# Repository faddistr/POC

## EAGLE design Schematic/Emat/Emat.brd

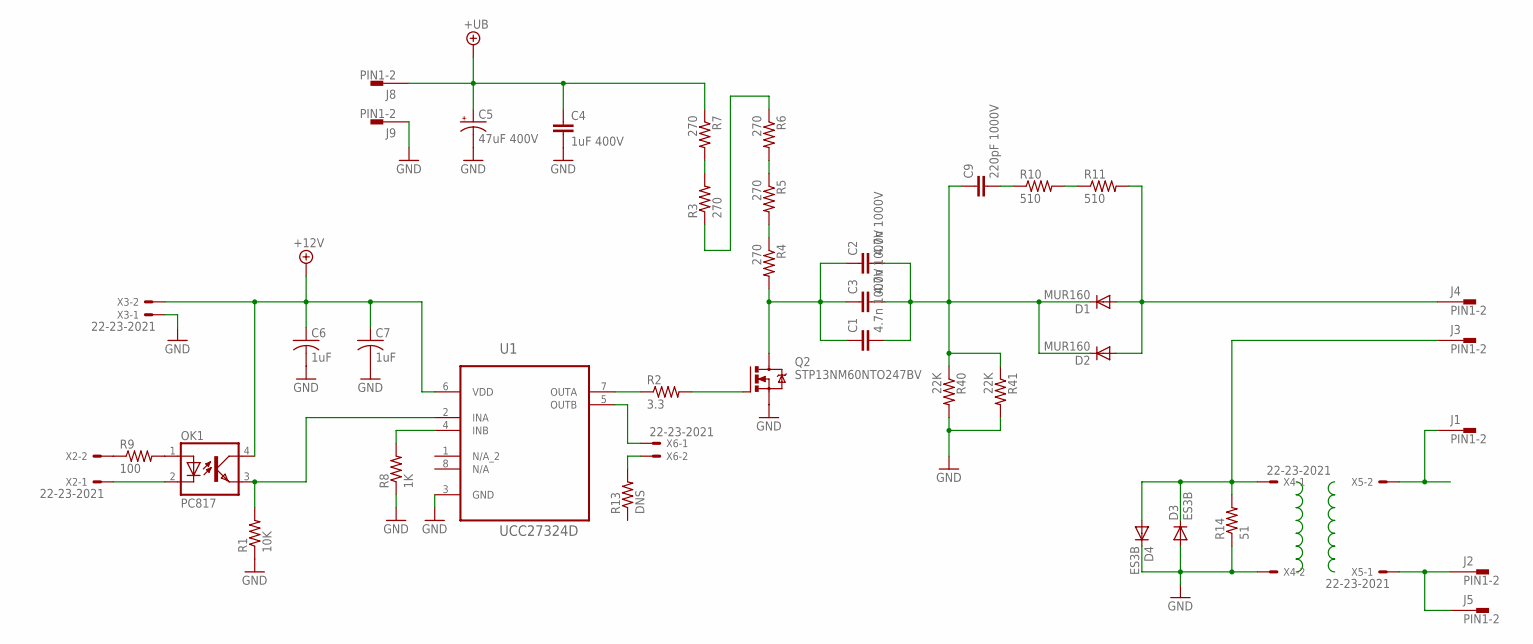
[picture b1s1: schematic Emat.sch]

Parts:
C1, C2, C3: 4.7n 1000V; C10B4
C4: 1uF 400V; C27.5B13
C5: 47uF 400V; SANYO-OSCON_G
C6, C7: 1uF; C0805
C9: 220pF 1000V; C075-042X103
D1, D2: MUR160; DO41-10
D3, D4: ES3B; SMC
J1, J2, J3, J4, J5, J8, J9: PIN1-2; 62221
OK1: PC817; DIL04
Q2: STP13NM60NTO247BV; TO247BV
R1: 10K; R1206
R2: 3.3; R1206
R3, R4, R5, R6, R7: 270; R2512
R8: 1K; R1206
R9: 100; R1206
R10, R11: 510; R1206
R13: DNS; R1206
R14: 51; R1206
R40, R41: 22K; R2512
U1: UCC27324D; SOIC127P600X175-8N
X2, X3, X4, X5, X6: 22-23-2021

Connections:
+12V: C6.1, C7.1, OK1.4 (COL), U1.6 (VDD), X3.2
+UB: C4.1, C5.+, J8.1, R7.1
GND: C4.2, C5.-, C6.2, C7.2, D3.A, D4.C, J9.1, Q2.S, R1.1, R8.1, R14.1, R40.2, R41.2, U1.3 (GND), X3.1, X4.2
unnamed: OK1.3 (EMIT), R1.2, U1.2 (INA)
unnamed: R2.1, U1.7 (OUTA)
unnamed: Q2.G, R2.2
unnamed: C1.1, C2.1, C3.1, Q2.D, R4.2
unnamed: R4.1, R5.2
unnamed: R5.1, R6.2
unnamed: R3.1, R6.1
unnamed: R3.2, R7.2
unnamed: J1.1, X5.2
unnamed: R8.2, U1.4 (INB)
unnamed: U1.5 (OUTB), X6.1
unnamed: C9.2, R10.1
unnamed: R10.2, R11.1
unnamed: D1.A, D2.A, J4.1, R11.2
unnamed: C1.2, C2.2, C3.2, C9.1, D1.C, D2.C, R40.1, R41.1
unnamed: OK1.1 (A), R9.2
unnamed: R9.1, X2.2
unnamed: OK1.2 (C), X2.1
unnamed: D3.C, D4.A, J3.1, R14.2, X4.1
unnamed: R13.2, X6.2
unnamed: J2.1, J5.1, X5.1

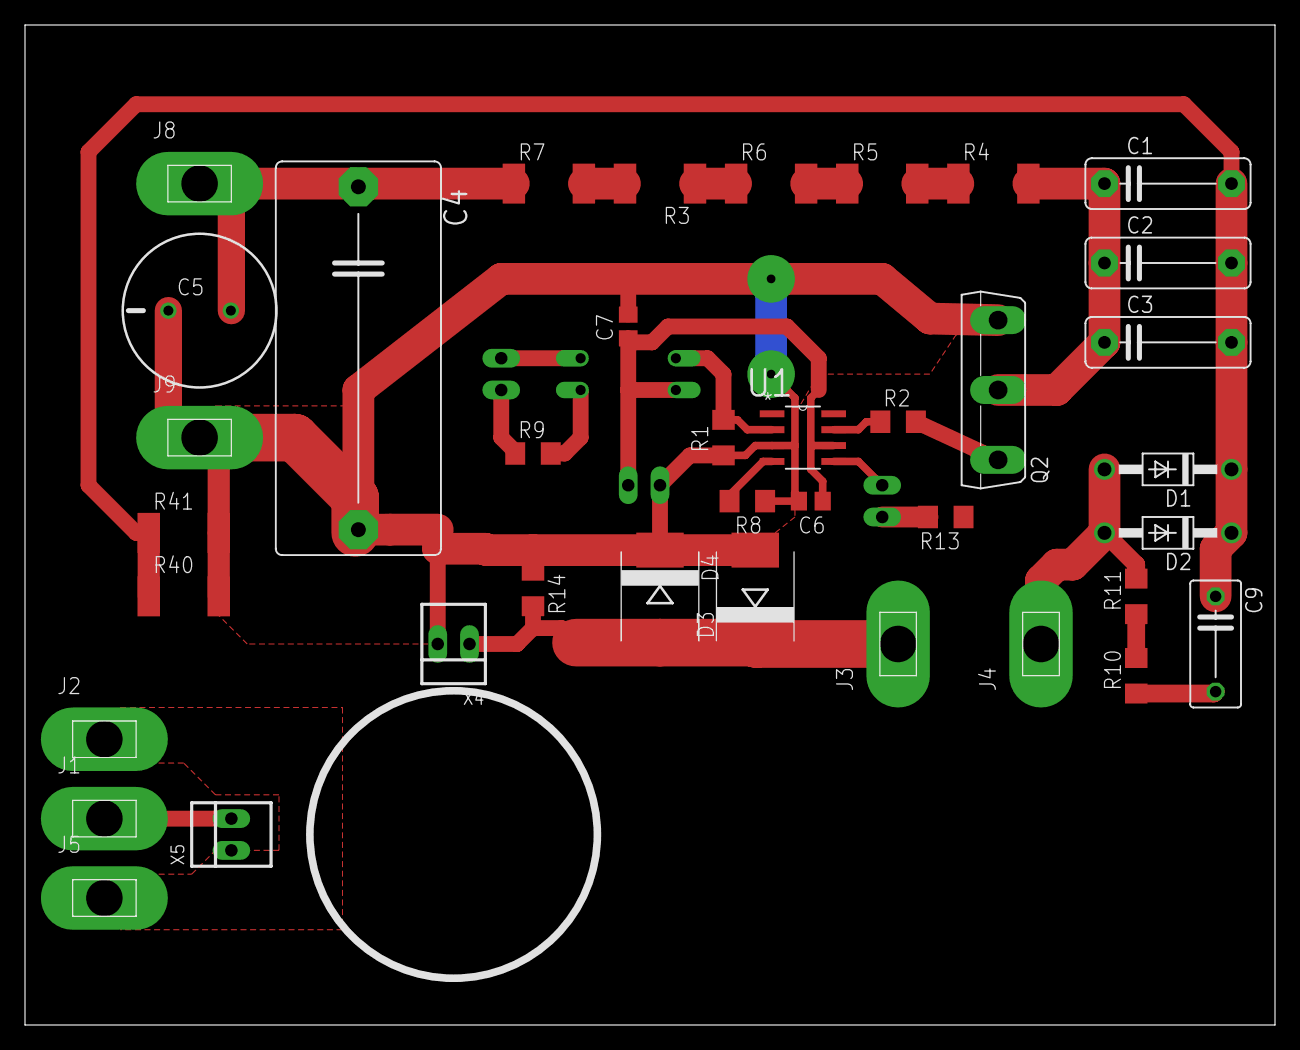
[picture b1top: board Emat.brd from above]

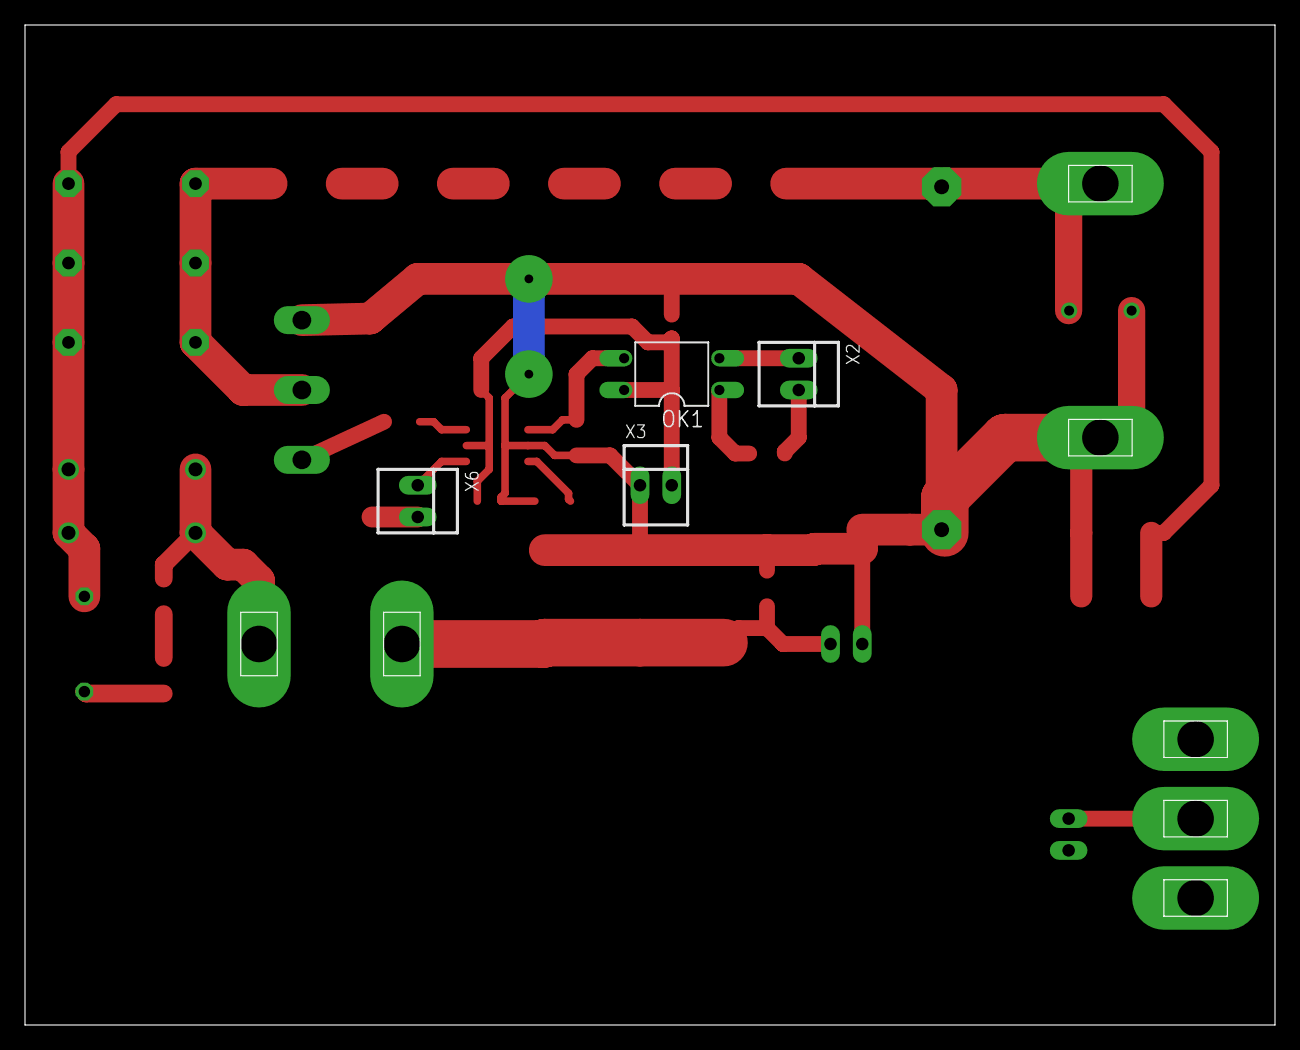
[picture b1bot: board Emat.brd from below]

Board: 2 copper layers, 100.0 x 80.0 mm, 42 parts (4 on the bottom side), 24 nets.

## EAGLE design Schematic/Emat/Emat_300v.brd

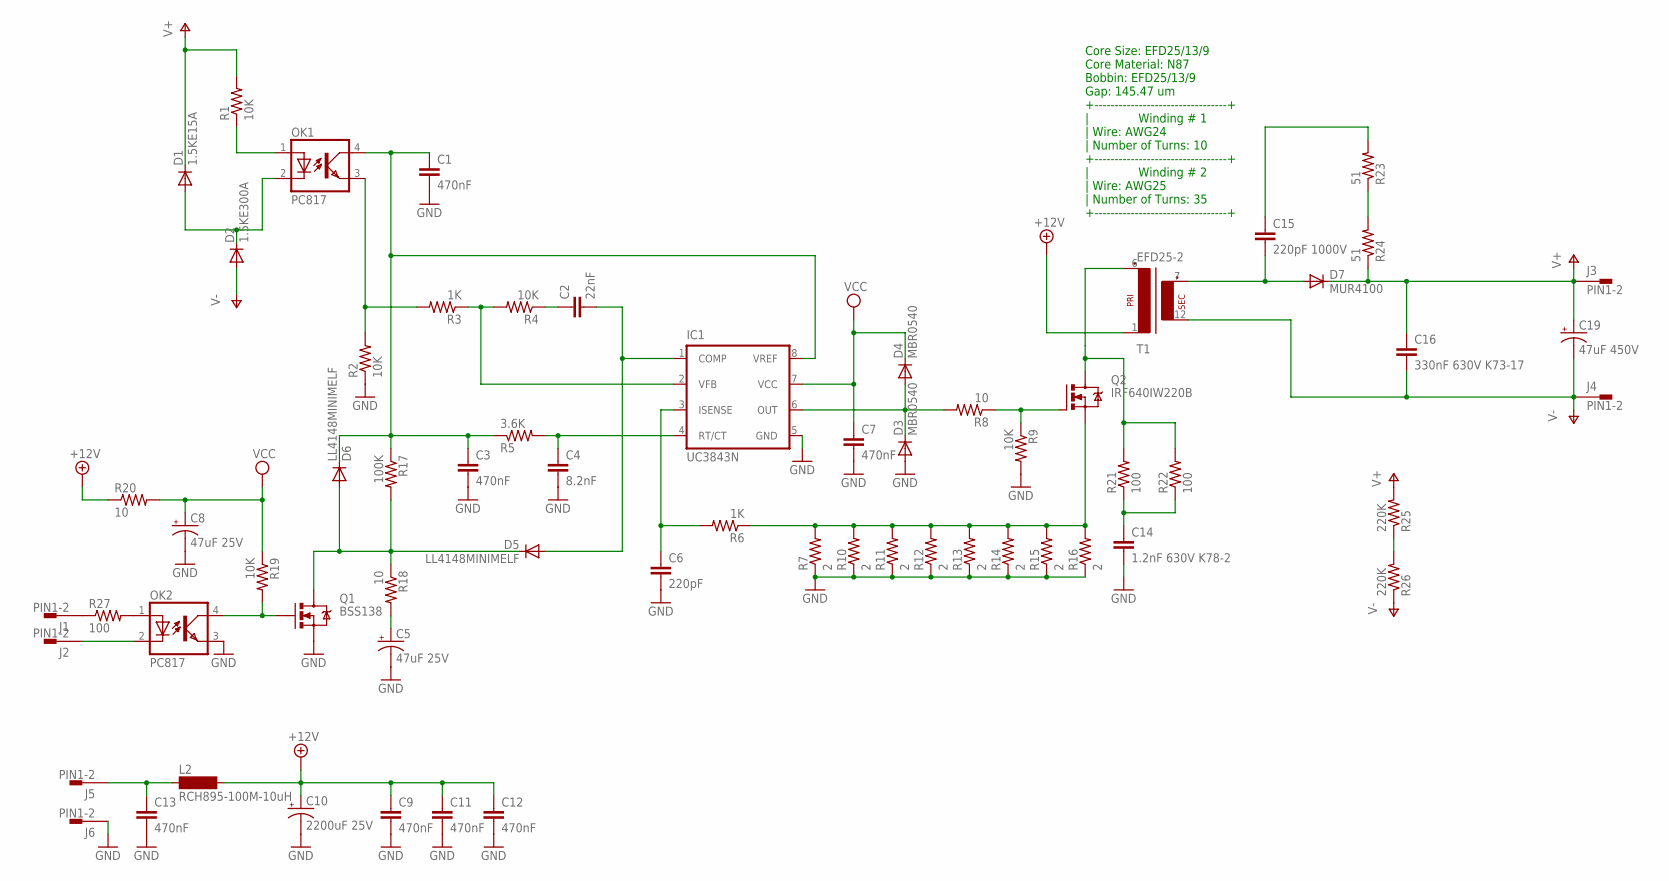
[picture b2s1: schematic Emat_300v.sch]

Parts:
C1, C3, C7, C9, C11, C12, C13: 470nF; C0805
C2: 22nF; C0805
C4: 8.2nF; C0805
C5, C8: 47uF 25V; E5-8,5
C6: 220pF; C0805
C10: 2200uF 25V; E7,5-18
C14: 1.2nF 630V K78-2; C150-064X183
C15: 220pF 1000V; C075-042X103
C16: 330nF 630V K73-17; C225-062X268
C19: 47uF 450V; E7,5-18
D1: 1.5KE15A; DO201-15
D2: 1.5KE300A; DO201-15
D3, D4: MBR0540; SOD123
D5, D6: LL4148MINIMELF; MINIMELF
D7: MUR4100; DO201-15
IC1: UC3843N; DIL08
J1, J2, J3, J4, J5, J6: PIN1-2; 62221
L2: RCH895-100M-10uH; BS11
OK1, OK2: PC817; DIL04
Q1: BSS138; SOT23-3
Q2: IRF640IW220B; IW220B
R1, R2, R4, R9, R19: 10K; R1206
R3, R6: 1K; R1206
R5: 3.6K; R1206
R7, R10, R11, R12, R13, R14, R15, R16: 2; R1206
R8, R18, R20: 10; R1206
R17: 100K; R1206
R21, R22: 100; R2512
R23, R24: 51; R1206
R25, R26: 220K; R1206
R27: 100; R1206
T1: EFD25-2; EFD25

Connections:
+12V: C9.1, C10.+, C11.1, C12.1, L2.2, R20.1, T1.1
GND: C1.2, C3.2, C4.2, C5.-, C6.2, C7.2, C8.-, C9.2, C10.-, C11.2, C12.2, C13.2, C14.2, D3.A, IC1.5 (GND), J6.1, OK2.3 (EMIT), Q1.2 (S), R2.1, R7.1, R9.2, R10.1, R11.1, R12.1, R13.1, R14.1, R15.1, R16.1
unnamed: D1.A, D2.C, OK1.2 (C)
unnamed: R25.1, R26.2
unnamed: OK1.1 (A), R1.1
unnamed: C5.+, R18.2
unnamed: OK1.3 (EMIT), R2.2, R3.2
unnamed: IC1.2 (VFB), R3.1, R4.2
unnamed: C2.1, R4.1
unnamed: C2.2, D5.A, IC1.1 (COMP)
unnamed: C4.1, IC1.4 (RT/CT), R5.2
unnamed: C6.1, IC1.3 (ISENSE), R6.2
unnamed: D3.C, D4.A, IC1.6 (OUT), R8.2
unnamed: Q2.G, R8.1, R9.1
unnamed: Q2.S, R6.1, R7.2, R10.2, R11.2, R12.2, R13.2, R14.2, R15.2, R16.2
unnamed: C1.1, C3.1, D6.C, IC1.8 (VREF), OK1.4 (COL), R5.1, R17.1
unnamed: D5.C, D6.A, Q1.3 (D), R17.2, R18.1
unnamed: C13.1, J5.1, L2.1
unnamed: OK2.4 (COL), Q1.1 (G), R19.2
unnamed: OK2.1 (A), R27.2
unnamed: J2.1, OK2.2 (C)
unnamed: Q2.D, R21.2, R22.2, T1.6 (P2)
unnamed: C14.1, R21.1, R22.1
unnamed: C15.2, D7.A, T1.7 (S1)
unnamed: J1.1, R27.1
unnamed: R23.1, R24.2
unnamed: C15.1, R23.2
V+: C16.1, C19.+, D1.C, D7.C, J3.1, R1.2, R24.1, R25.2
V-: C16.2, C19.-, D2.A, J4.1, R26.1, T1.12 (S2)
VCC: C7.1, C8.+, D4.C, IC1.7 (VCC), R19.1, R20.2

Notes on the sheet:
Core Size: EFD25/13/9 Core Material: N87 Bobbin: EFD25/13/9 Gap: 145.47 um +---------------------------------+ | Winding # 1 | Wire: AWG24 | Number of Turns: 10 +---------------------------------+ | Winding # 2 | Wire: AWG25 | Number of Turns: 35 +---------------------------------+

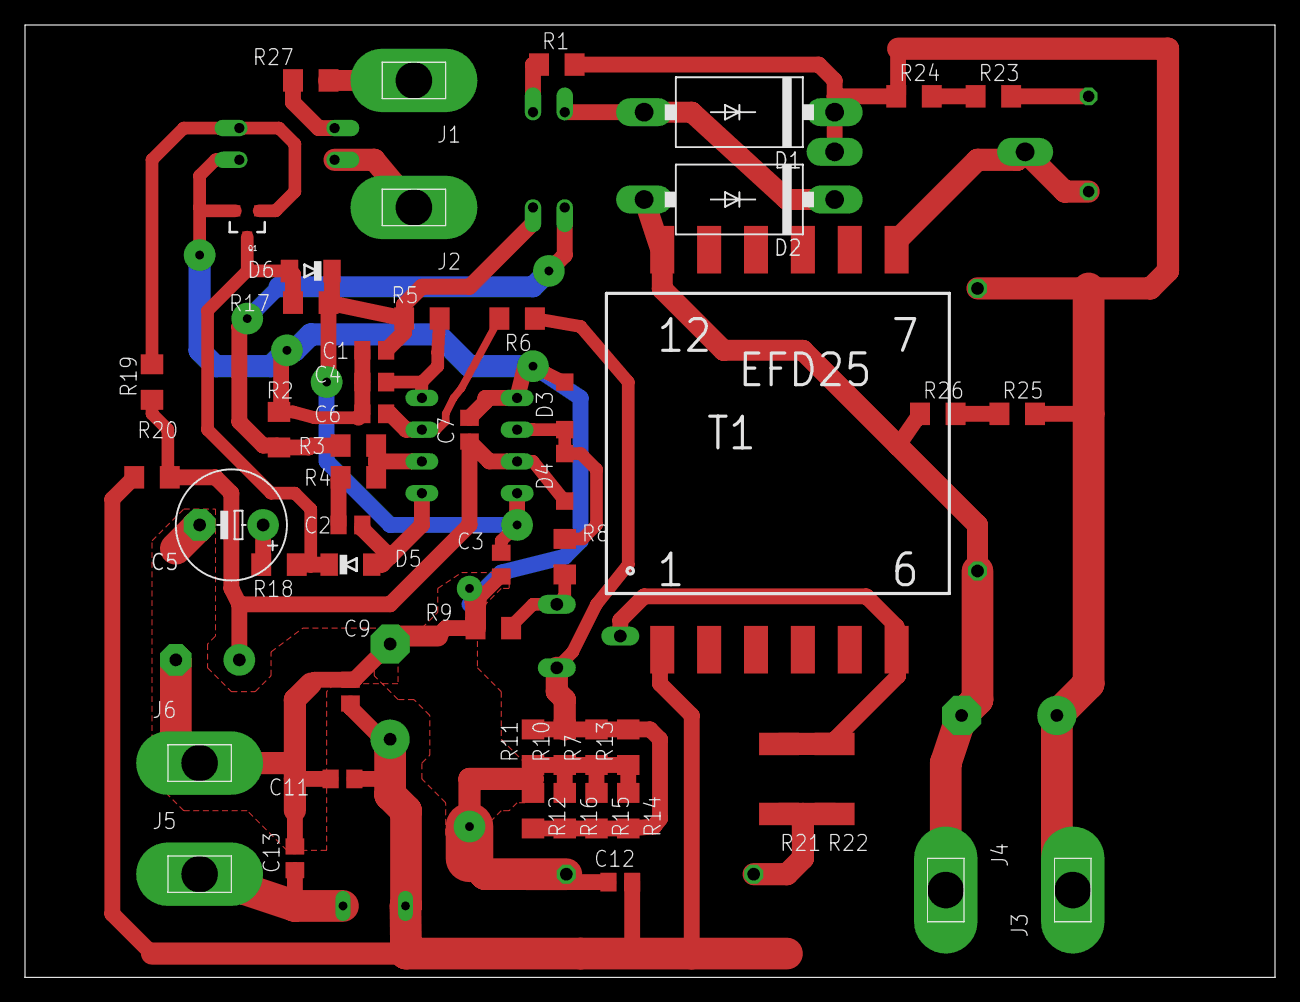
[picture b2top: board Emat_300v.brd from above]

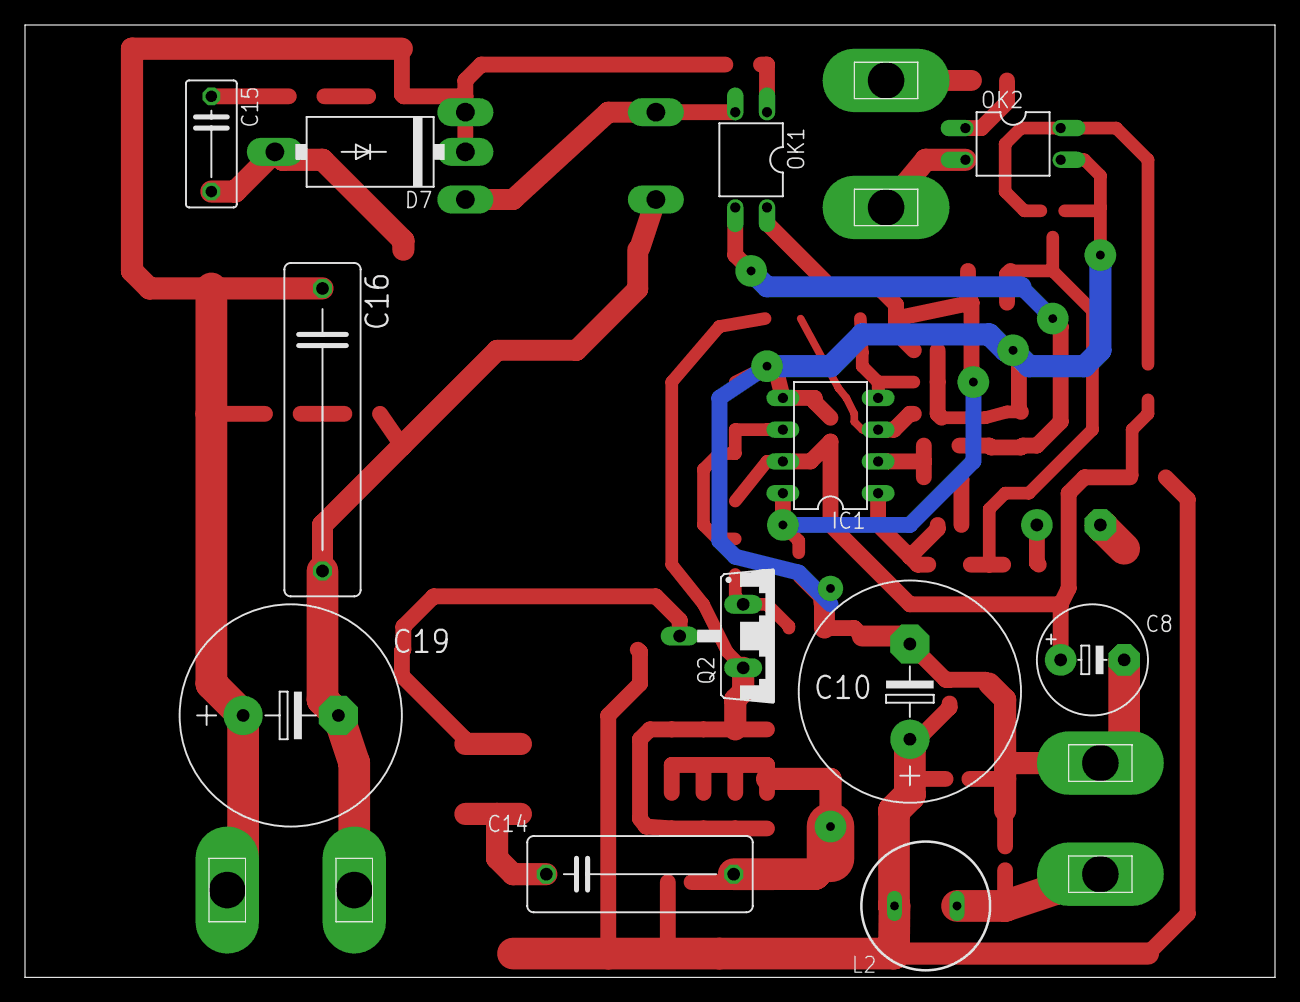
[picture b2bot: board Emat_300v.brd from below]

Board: 2 copper layers, 100.0 x 76.2 mm, 64 parts (12 on the bottom side), 30 nets.

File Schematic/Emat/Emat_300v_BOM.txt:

Partlist exported from D:/workspace/EMAT/POC/Schematic/Emat/Emat_300v.sch at 4/7/2016 10:36 AM

Qty Value             Device                Package      Parts                                 Description
1   EFD25             EFD25                 EFD25        T1                                    TRANSFORMER
1   UC3843N           UC3843N               DIL08        IC1                                   SMPS Controller
1   BSS138            MOSFET-NCHANNELBSS138 SOT23-3      Q1                                    Common NMOSFET Parts
1   IRF640IW220B      IRF640IW220B          IW220B       Q2                                    HEXFET Power MOSFET
2   LL4148MINIMELF    LL4148MINIMELF        MINIMELF     D5, D6                                DIODE              
2   MBR0540           DIODE-SOD123          SOD123       D3, D4                                DIODE              
1   MUR4100           DIODE-DO201-15        DO201-15     D7                                    DIODE              
2   1.5KE15A          DIODE-DO201-15        DO201-15     D1, D2                                DIODE
2   PC817             PC817                 DIL04        OK1, OK2                              SHARP OPTO COUPLER
2   47uF 25V          CPOL-USE5-8.5         E5-8,5       C5, C8                                POLARIZED CAPACITOR
1   47uF 450V         CPOL-USE7.5-18        E7,5-18      C19                                   POLARIZED CAPACITOR
1   2200uF 25V        CPOL-USE7.5-18        E7,5-18      C10                                   POLARIZED CAPACITOR
1   1.2nF 630V K78-2  C-EU150-064X183       C150-064X183 C14                                   CAPACITOR
1   330nF 630V K73-17 C-EU225-062X268       C225-062X268 C16                                   CAPACITOR
1   220pF 1000V       C-EU075-042X103       C075-042X103 C15                                   CAPACITOR
1   220pF             C-EUC0805             C0805        C6                                    CAPACITOR
1   22nF              C-EUC0805             C0805        C2                                    CAPACITOR
7   470nF             C-EUC0805             C0805        C1, C3, C7, C9, C11, C12, C13         CAPACITOR
1   8.2nF             C-EUC0805             C0805        C4                                    CAPACITOR
2   100               R-US_R2512            R2512        R21, R22                              RESISTOR
3   10                R-US_R1206            R1206        R8, R18, R20                          RESISTOR
1   100K              R-US_R1206            R1206        R17                                   RESISTOR
5   10K               R-US_R1206            R1206        R1, R2, R4, R9, R19                   RESISTOR
2   1K                R-US_R1206            R1206        R3, R6                                RESISTOR
8   2                 R-US_R1206            R1206        R7, R10, R11, R12, R13, R14, R15, R16 RESISTOR
2   220K              R-US_R1206            R1206        R25, R26                              RESISTOR
1   3.6K              R-US_R1206            R1206        R5                                    RESISTOR
2   51                R-US_R1206            R1206        R23, R24                              RESISTOR
1   RCH895-100M-10uH  RCH-89511             BS11         L2                                    INDUCTOR
6   PIN1-2            PIN1-2                62221        J1, J2, J3, J4, J5, J6                CONN

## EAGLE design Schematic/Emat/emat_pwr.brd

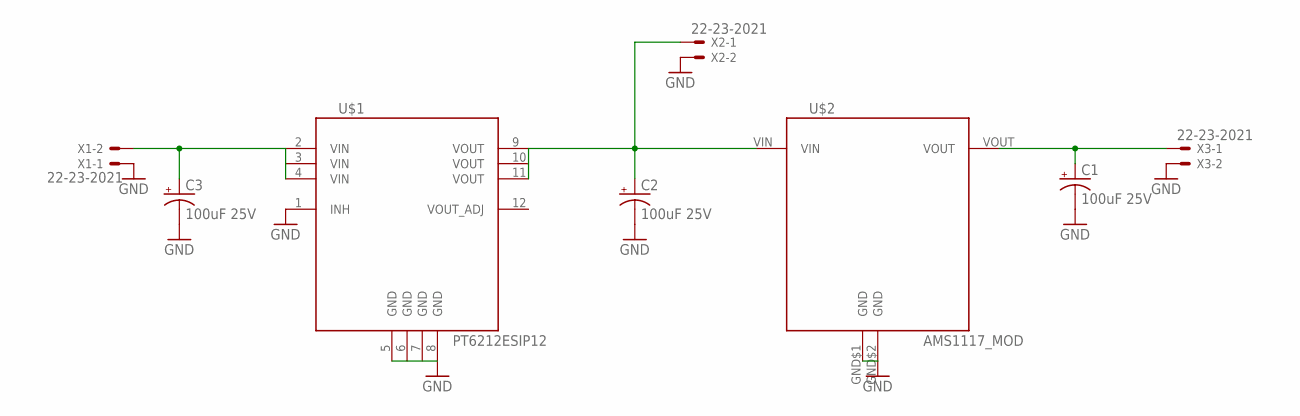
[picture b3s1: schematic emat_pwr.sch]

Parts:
C1, C2, C3: 100uF 25V; CPOL-RADIAL-100UF-25V
U$1: PT6212ESIP12; PT621X
U$2: AMS1117_MOD
X1, X2, X3: 22-23-2021

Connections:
GND: C1.2 (-), C2.2 (-), C3.2 (-), U$1.1 (INH), U$1.5 (GND), U$1.6 (GND), U$1.7 (GND), U$1.8 (GND), U$2.GND$1 (GND), U$2.GND$2 (GND), X1.1, X2.2, X3.2
unnamed: C2.1 (+), U$1.9 (VOUT), U$1.11 (VOUT), U$2.VIN, X2.1
unnamed: C1.1 (+), U$2.VOUT, X3.1
unnamed: C3.1 (+), U$1.2 (VIN), U$1.4 (VIN), X1.2
VIN: U$1.3 (VIN)
VOUT: U$1.10 (VOUT)
VOUT_ADJ: U$1.12 (VOUT_ADJ)

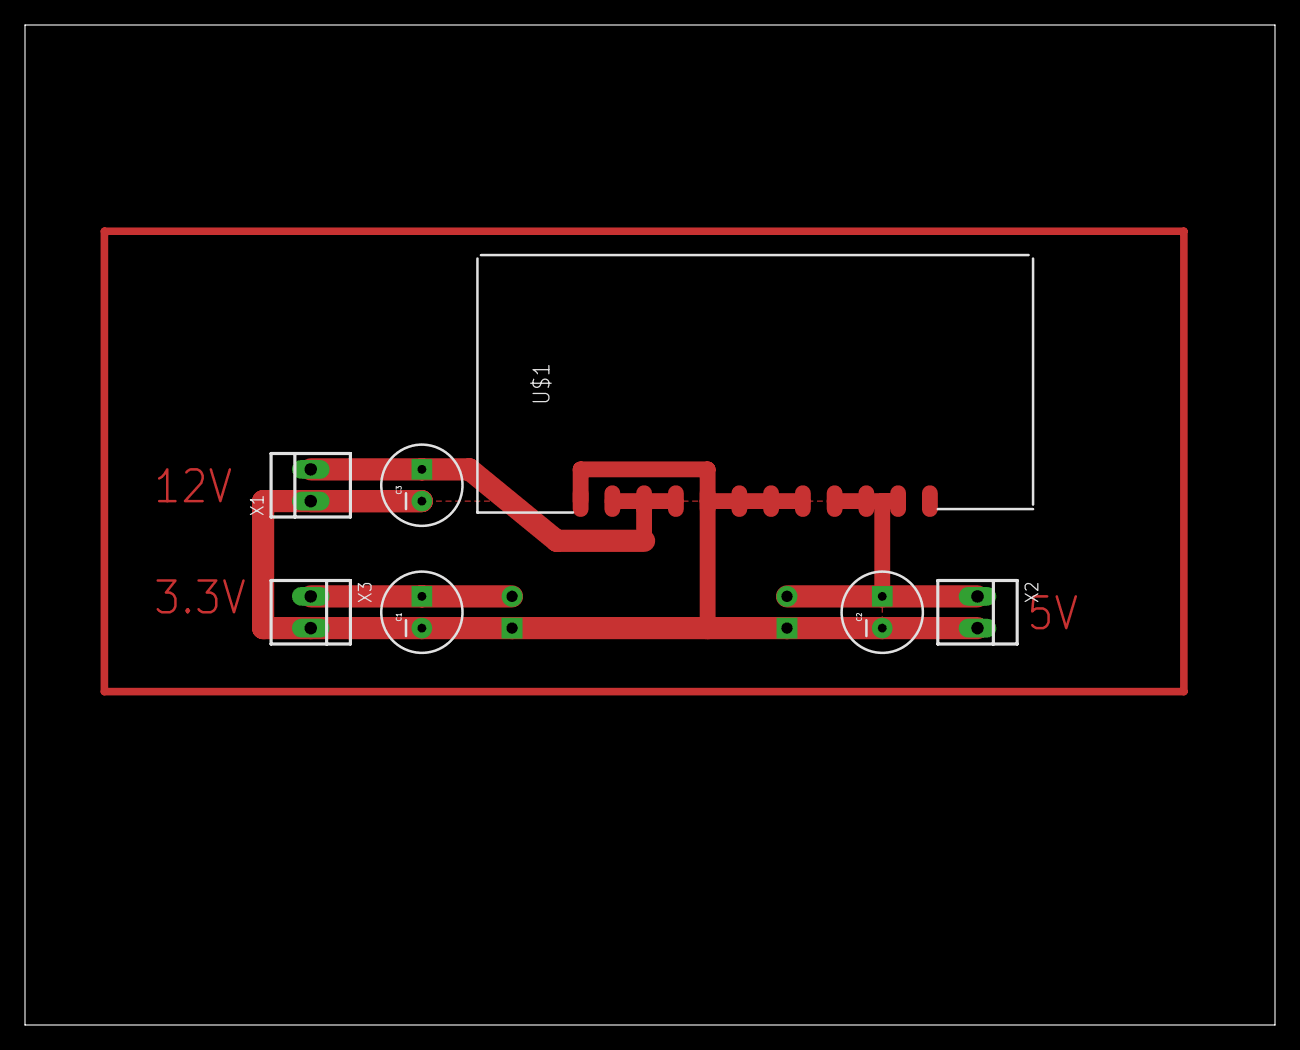
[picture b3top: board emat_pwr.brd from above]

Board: 2 copper layers, 100.0 x 80.0 mm, 8 parts (1 on the bottom side), 4 nets.

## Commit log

2016-03-28 Add original soft with fixes
2016-03-31 Add docs, make minor change in java soft
2016-03-31 Add stm32 generator
2016-03-31 Initial implementation for stm32 Discovery board
    Includes USB-To-Serial and terminal console.
2016-03-31 Add ignore settings.
2016-03-31 Add External interrupt on PA1
2016-03-31 Add timer support.
2016-03-31 Add event_queue file.
2016-04-01 Add timer implementation.
2016-04-01 Add terminal command.
2016-04-01 Add pulse shift functionality
2016-04-01 Remote TIM1 from Cube configuration.
2016-04-01 Add pulse width/offset change commands.
2016-04-03 implement Generator class untested.
2016-04-04 Integrate class Generator into program
2016-04-04 Add schematic
2016-04-04 Drop javax.comm replace by gnu.io.rxtx
2016-04-04 Set width and set offset commands works
2016-04-04 Minor fixes
2016-04-04 Add ability to change width and offset online
2016-04-05 HV Key schematic done.
2016-04-05 Added +300V schematic (not full)
2016-04-06 Further work on schematic.
2016-04-06 300V pcb done
2016-04-07 300V PCB modified, BOM added.
2016-04-07 Add BOM.
2016-04-07 Remove pull up on sync input PE.11
2016-04-07 Add resistor before opto-coupler.
    To enable direct controll from STM32.
2016-04-08 Add switch tracing.
2016-04-11 Modify board to fit to pcb.
2016-04-11 Remove unused stuff.
2016-04-13 Add power supply board.
2016-04-14 Add pcb images
2016-04-14 Add width calculation
2016-04-20 Add HV On Off command.
2016-04-20 Fix transformer wiring.
2016-04-20 Fix schematic. 1.5KE300 added.
2016-04-20 Put initial pulse on the right place.
    Offset = 403 us
    Width = 1 us
2016-04-20 Add filter
2016-04-21 Add filter config, add width finder algorithm
2016-04-22 fix image
2016-04-23 Switch HV off while pulse generated.
2016-04-25 reduce aquire speed to 10Hz
2016-04-26 Add avd
2016-04-26 Add offset feature
2016-04-26 Fix avd
2016-04-28 Add dlls
2016-04-28 Add missed dlls
2016-04-28 Add jars
2016-04-29 Fix release build of native library
2016-04-29 Add release version of dll binary
2016-04-29 Change build of java project, replace debug version of native dll with release one
2016-04-29 Add everything.
2016-04-29 Remove logs

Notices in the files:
parts and their libraries:
SparkFun-DiscreteSemi: Licensing: Creative Commons ShareAlike 4.0 International - https://creativecommons.org/licenses/by-sa/4.0
